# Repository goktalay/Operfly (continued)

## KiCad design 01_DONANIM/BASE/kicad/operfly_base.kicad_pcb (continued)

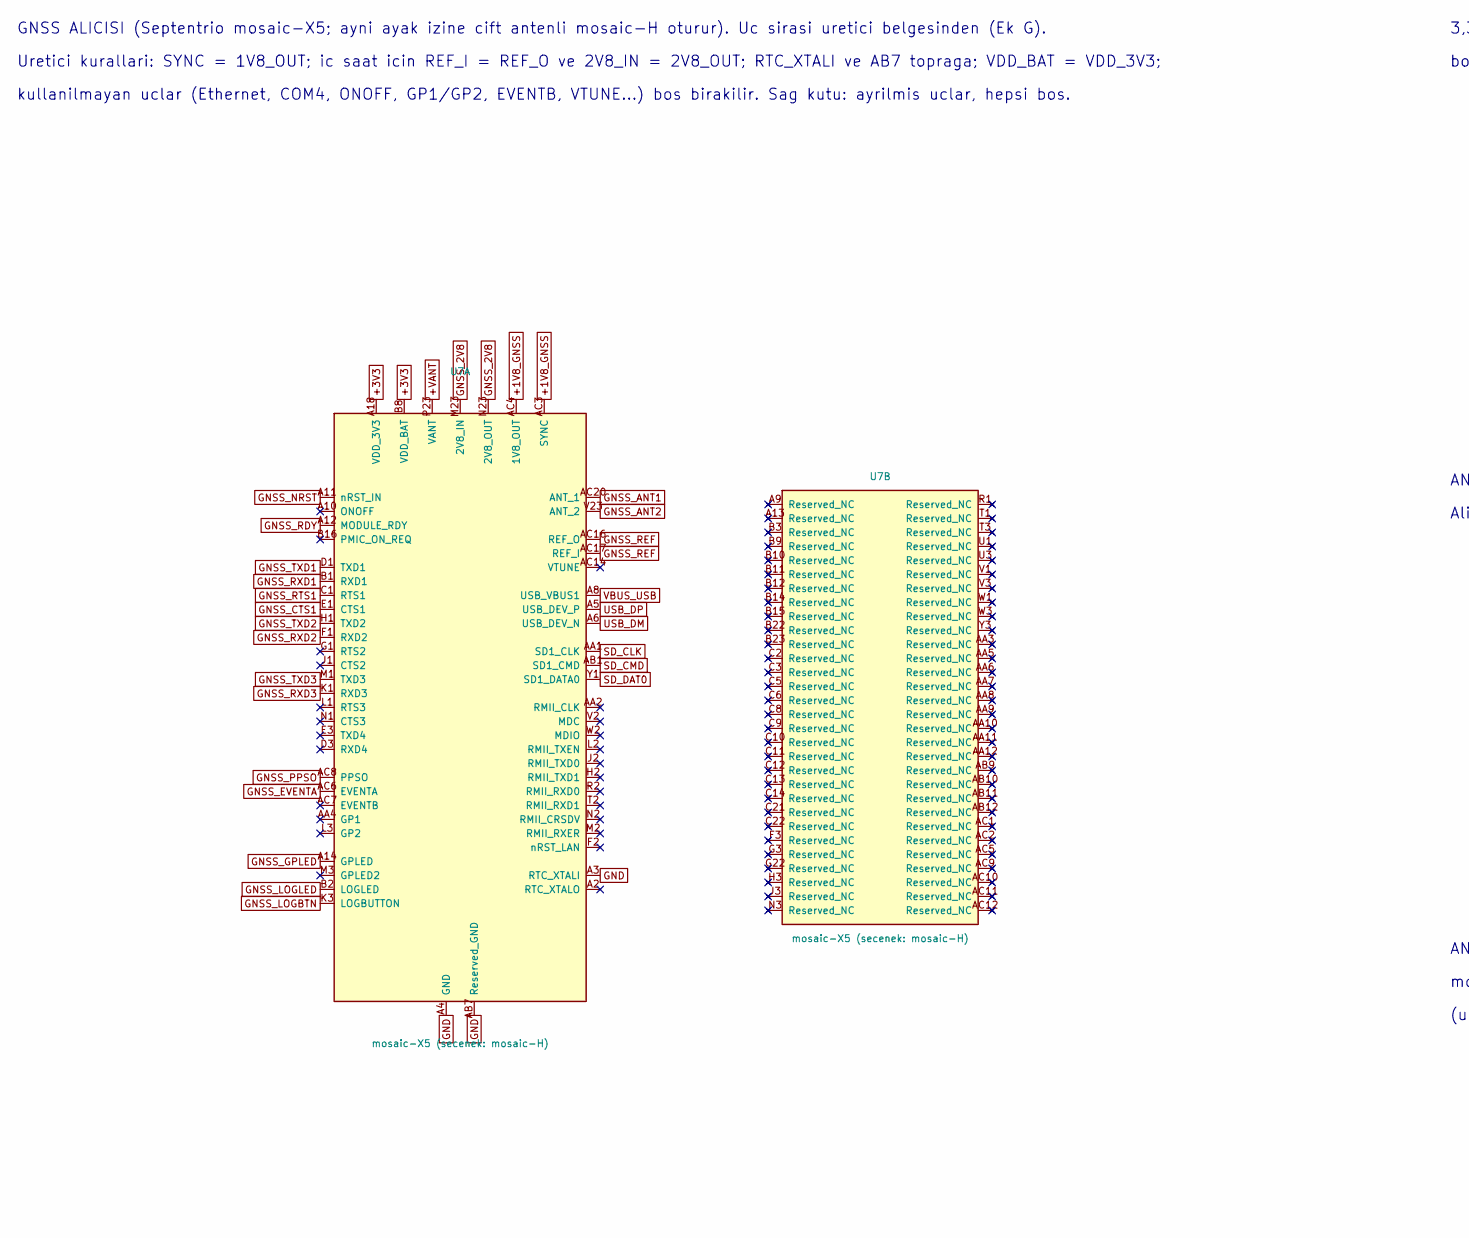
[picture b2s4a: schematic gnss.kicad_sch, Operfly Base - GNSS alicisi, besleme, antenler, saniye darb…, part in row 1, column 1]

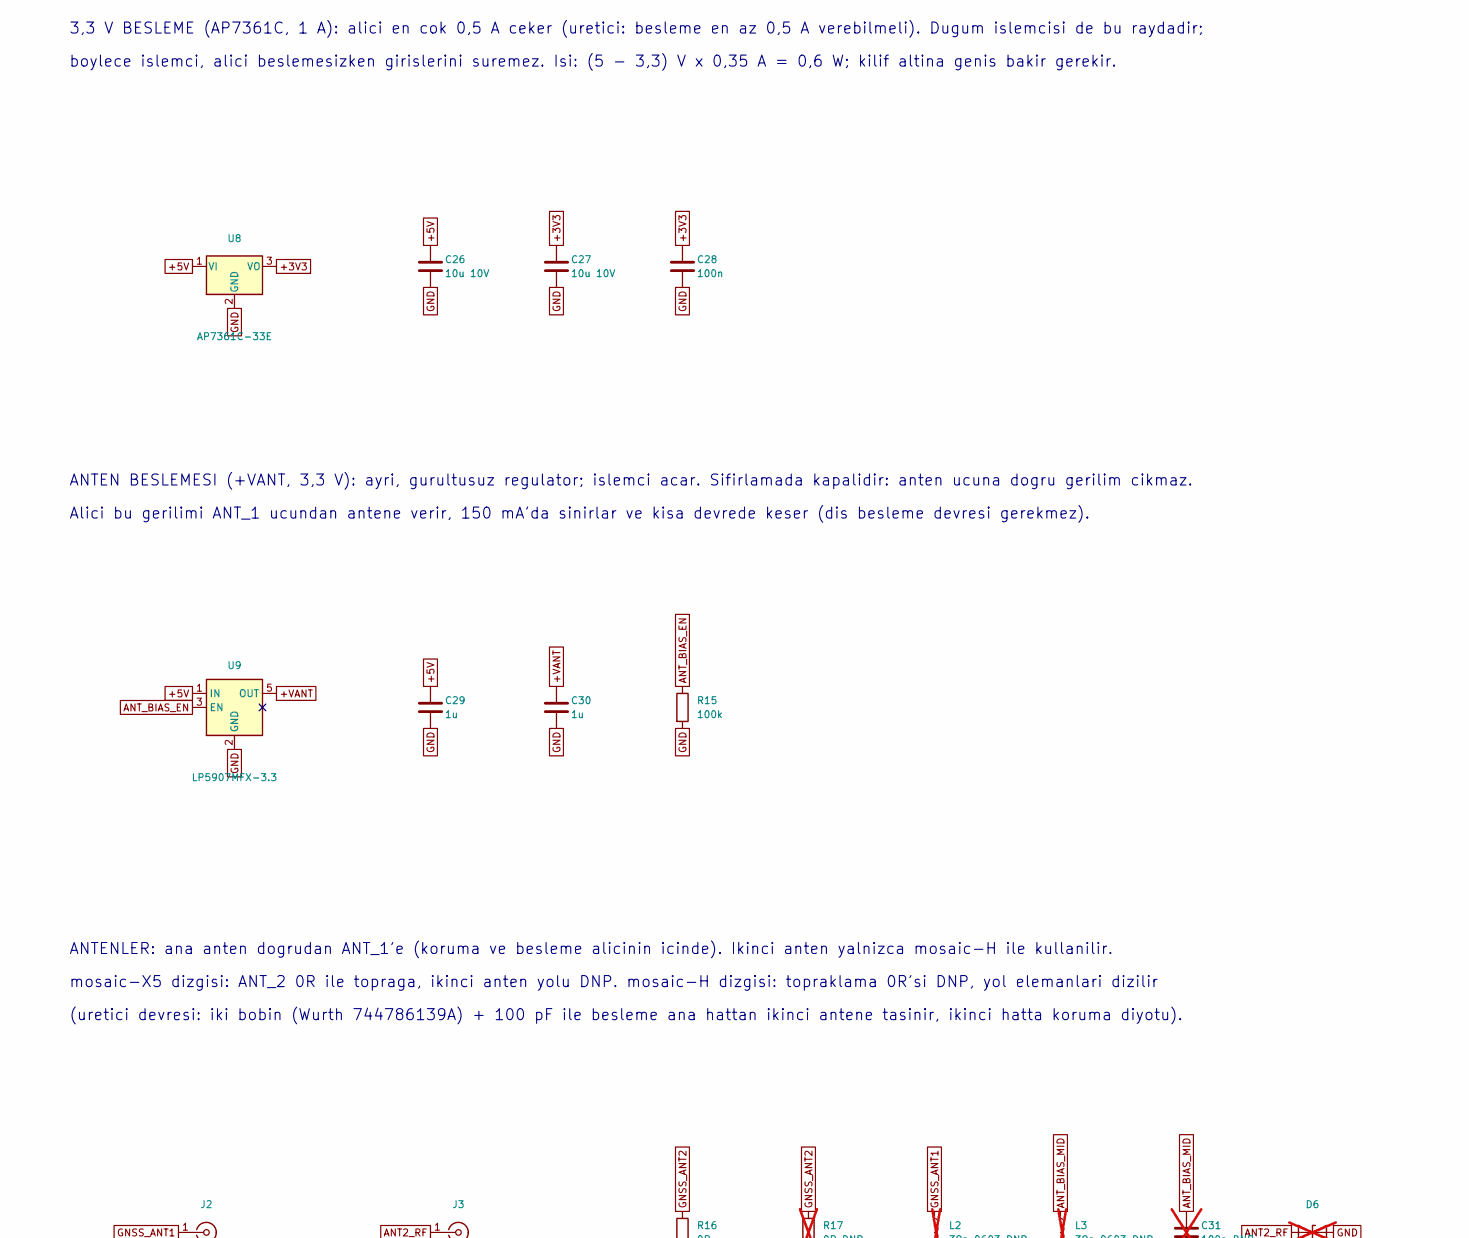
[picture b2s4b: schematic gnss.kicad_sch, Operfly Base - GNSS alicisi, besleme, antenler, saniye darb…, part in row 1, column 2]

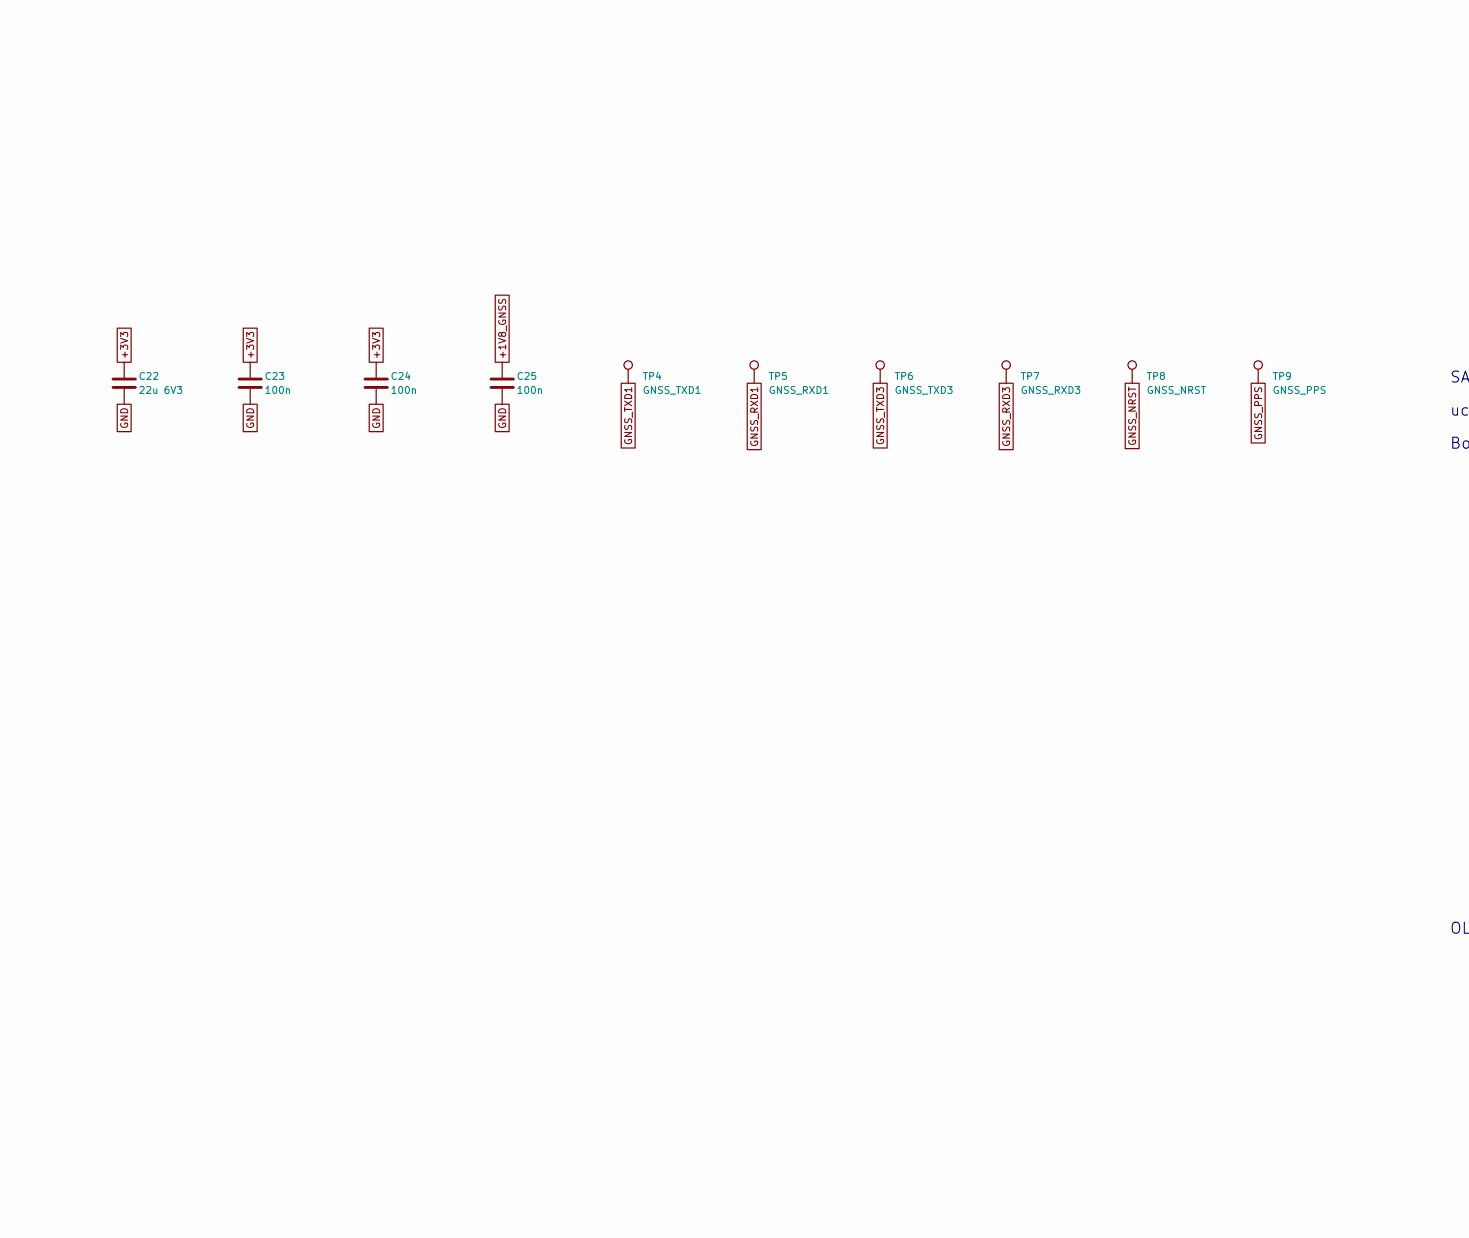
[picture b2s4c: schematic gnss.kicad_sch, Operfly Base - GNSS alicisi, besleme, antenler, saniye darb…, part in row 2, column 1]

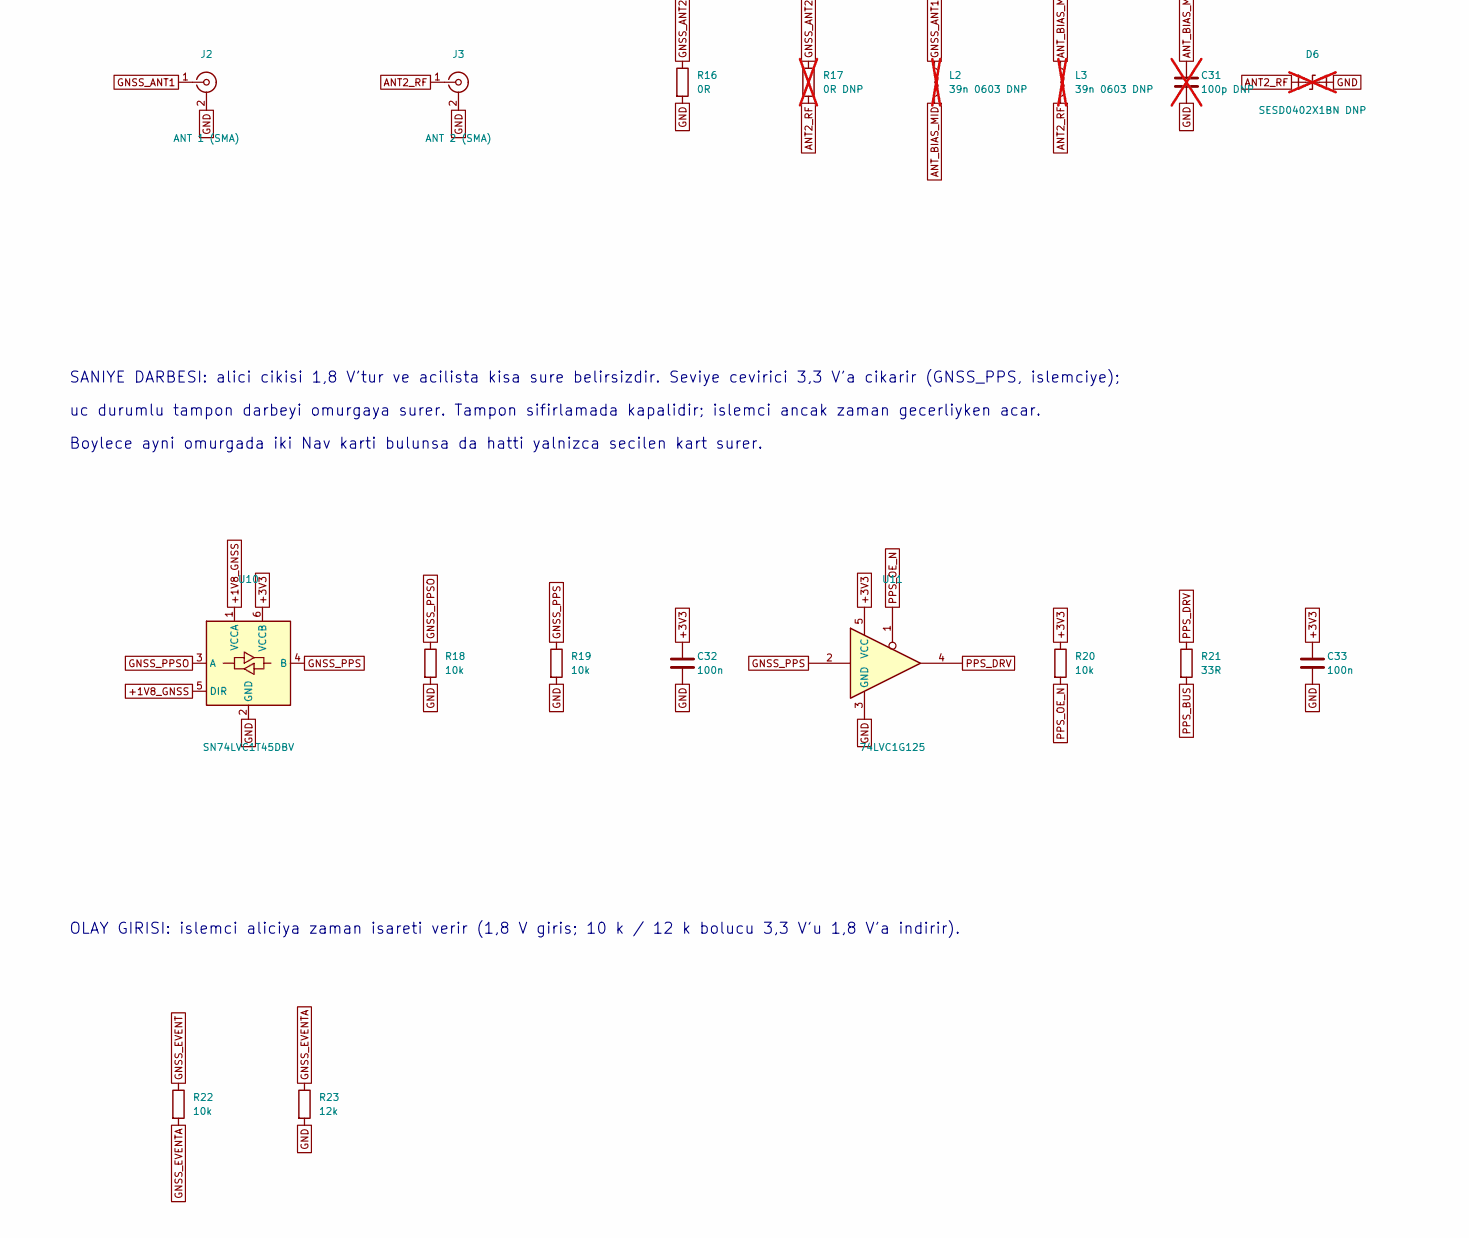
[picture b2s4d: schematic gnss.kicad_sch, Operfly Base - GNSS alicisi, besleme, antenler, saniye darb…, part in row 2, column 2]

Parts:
C22: 22u 6V3; C_0805_2012Metric
C23, C24, C25, C28, C32, C33: 100n; C_0402_1005Metric
C26, C27: 10u 10V; C_0805_2012Metric
C29, C30: 1u; C_0402_1005Metric
C31: 100p DNP; C_0402_1005Metric; not fitted
D6: SESD0402X1BN DNP; D_0402_1005Metric; not fitted
J2: ANT 1 (SMA); SMA_Amphenol_132289_EdgeMount
J3: ANT 2 (SMA); SMA_Amphenol_132289_EdgeMount
L2, L3: 39n 0603 DNP; L_0603_1608Metric; not fitted
R15: 100k; R_0402_1005Metric
R16: 0R; R_0402_1005Metric
R17: 0R DNP; R_0402_1005Metric; not fitted
R18, R19, R20, R22: 10k; R_0402_1005Metric
R21: 33R; R_0402_1005Metric
R23: 12k; R_0402_1005Metric
TP4: GNSS_TXD1; TestPoint_Pad_D1.0mm
TP5: GNSS_RXD1; TestPoint_Pad_D1.0mm
TP6: GNSS_TXD3; TestPoint_Pad_D1.0mm
TP7: GNSS_RXD3; TestPoint_Pad_D1.0mm
TP8: GNSS_NRST; TestPoint_Pad_D1.0mm
TP9: GNSS_PPS; TestPoint_Pad_D1.0mm
U7: mosaic-X5 (secenek: mosaic-H); Septentrio_mosaic_LGA-239_31x31mm_P1.27mm
U8: AP7361C-33E; SOT-223-3_TabPin2
U9: LP5907MFX-3.3; SOT-23-5
U10: SN74LVC1T45DBV; SOT-23-6
U11: 74LVC1G125; SOT-353_SC-70-5

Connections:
+1V8_GNSS: C25.1, U7.AC3 (SYNC), U7.AC4 (1V8_OUT), U10.1 (VCCA), U10.5 (DIR)
+3V3: C22.1, C23.1, C24.1, C27.1, C28.1, C32.1, C33.1, R20.1, U7.A18 (VDD_3V3), U7.A19 (VDD_3V3), U7.A20 (VDD_3V3), U7.B8 (VDD_BAT), U7.B18 (VDD_3V3), U7.B19 (VDD_3V3), U7.B20 (VDD_3V3), U7.C18 (VDD_3V3), U7.C19 (VDD_3V3), U7.C20 (VDD_3V3), U8.3 (VO), U10.6 (VCCB), U11.5 (VCC); also elsewhere on the board
+5V: C26.1, C29.1, U8.1 (VI), U9.1 (IN); also elsewhere on the board
+VANT: C30.1, U7.P23 (VANT), U7.R23 (VANT), U9.5 (OUT)
ANT2_RF: D6.1 (A1), J3.1 (In), L3.2, R17.2
ANT_BIAS_EN: R15.1, U9.3 (EN); also elsewhere on the board
ANT_BIAS_MID: C31.1, L2.2, L3.1
GND: C22.2, C23.2, C24.2, C25.2, C26.2, C27.2, C28.2, C29.2, C30.2, C31.2, C32.2, C33.2, D6.2 (A2), J2.2 (Ext), J3.2 (Ext), R15.2, R16.2, R18.2, R19.2, R23.2, U7.A3 (RTC_XTALI), U7.A4 (GND), U7.A7 (GND), U7.A15 (GND), U7.A16 (GND), U7.A17 (GND), U7.A21 (GND), U7.A22 (GND), U7.A23 (GND), U7.AA13 (GND), U7.AA14 (GND), U7.AA15 (GND), U7.AA16 (GND), U7.AA17 (GND), U7.AA18 (GND), U7.AA19 (GND), U7.AA20 (GND), U7.AA21 (GND), U7.AA22 (GND), U7.AA23 (GND), U7.AB2 (GND), U7.AB3 (GND), U7.AB4 (GND), U7.AB5 (GND), U7.AB6 (GND), U7.AB7 (Reserved_GND), U7.AB8 (GND), U7.AB13 (GND), U7.AB14 (GND), U7.AB15 (GND), U7.AB16 (GND), U7.AB17 (GND), U7.AB18 (GND), U7.AB19 (GND), U7.AB20 (GND), U7.AB21 (GND), U7.AB22 (GND), U7.AB23 (GND), U7.AC13 (GND), U7.AC15 (GND), U7.AC18 (GND), U7.AC19 (GND), U7.AC21 (GND), U7.AC22 (GND), U7.AC23 (GND), U7.B4 (GND), U7.B5 (GND), U7.B6 (GND), U7.B7 (GND), U7.B13 (GND), U7.B17 (GND), U7.B21 (GND), U7.C4 (GND), U7.C7 (GND), U7.C15 (GND), U7.C16 (GND), U7.C17 (GND), U7.C23 (GND), U7.D2 (GND), U7.D21 (GND), U7.D22 (GND), U7.D23 (GND), U7.E2 (GND), U7.E21 (GND), U7.E22 (GND), U7.E23 (GND), U7.F21 (GND), U7.F22 (GND), U7.F23 (GND), U7.G2 (GND), U7.G21 (GND), U7.G23 (GND), U7.H21 (GND), U7.H22 (GND), U7.H23 (GND), U7.J21 (GND), U7.J22 (GND), U7.J23 (GND), U7.K2 (GND), U7.K21 (GND), U7.K22 (GND), U7.K23 (GND), U7.L21 (GND), U7.L22 (GND), U7.L23 (GND), U7.M21 (GND), U7.M22 (GND), U7.N21 (GND), U7.N22 (GND), U7.P1 (GND), U7.P2 (GND), U7.P3 (GND), U7.P21 (GND), U7.P22 (GND), U7.R3 (GND), U7.R21 (GND), U7.R22 (GND), U7.T21 (GND), U7.T22 (GND), U7.T23 (GND), U7.U2 (GND), U7.U21 (GND), U7.U22 (GND), U7.U23 (GND), U7.V21 (GND), U7.V22 (GND), U7.W21 (GND), U7.W22 (GND), U7.W23 (GND), U7.Y2 (GND), U7.Y21 (GND), U7.Y22 (GND), U7.Y23 (GND), U8.2 (GND), U9.2 (GND), U10.2 (GND), U11.3 (GND); also elsewhere on the board
GNSS_2V8: U7.M23 (2V8_IN), U7.N23 (2V8_OUT)
GNSS_ANT1: J2.1 (In), L2.1, U7.AC20 (ANT_1)
GNSS_ANT2: R16.1, R17.1, U7.V23 (ANT_2)
GNSS_CTS1: U7.E1 (CTS1); also elsewhere on the board
GNSS_EVENT: R22.1; also elsewhere on the board
GNSS_EVENTA: R22.2, R23.1, U7.AC6 (EVENTA)
GNSS_GPLED: U7.A14 (GPLED); also elsewhere on the board
GNSS_LOGBTN: U7.K3 (LOGBUTTON); also elsewhere on the board
GNSS_LOGLED: U7.B2 (LOGLED); also elsewhere on the board
GNSS_NRST: TP8.1, U7.A11 (nRST_IN); also elsewhere on the board
GNSS_PPS: R19.1, TP9.1, U10.4 (B), U11.2; also elsewhere on the board
GNSS_PPSO: R18.1, U7.AC8 (PPSO), U10.3 (A)
GNSS_RDY: U7.A12 (MODULE_RDY); also elsewhere on the board
GNSS_REF: U7.AC16 (REF_O), U7.AC17 (REF_I)
GNSS_RTS1: U7.C1 (RTS1); also elsewhere on the board
GNSS_RXD1: TP5.1, U7.B1 (RXD1); also elsewhere on the board
GNSS_RXD2: U7.F1 (RXD2); also elsewhere on the board
GNSS_RXD3: TP7.1, U7.K1 (RXD3)
GNSS_TXD1: TP4.1, U7.D1 (TXD1); also elsewhere on the board
GNSS_TXD2: U7.H1 (TXD2); also elsewhere on the board
GNSS_TXD3: TP6.1, U7.M1 (TXD3)
PPS_BUS: R21.2; also elsewhere on the board
PPS_DRV: R21.1, U11.4
PPS_OE_N: R20.2, U11.1; also elsewhere on the board
SD_CLK: U7.AA1 (SD1_CLK); also elsewhere on the board
SD_CMD: U7.AB1 (SD1_CMD); also elsewhere on the board
SD_DAT0: U7.Y1 (SD1_DATA0); also elsewhere on the board
USB_DM: U7.A6 (USB_DEV_N); also elsewhere on the board
USB_DP: U7.A5 (USB_DEV_P); also elsewhere on the board
VBUS_USB: U7.A8 (USB_VBUS1); also elsewhere on the board

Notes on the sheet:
uc durumlu tampon darbeyi omurgaya surer. Tampon sifirlamada kapalidir; islemci ancak zaman gecerliyken acar.
GNSS ALICISI (Septentrio mosaic-X5; ayni ayak izine cift antenli mosaic-H oturur). Uc sirasi uretici belgesinden (Ek G).
(uretici devresi: iki bobin (Wurth 744786139A) + 100 pF ile besleme ana hattan ikinci antene tasinir, ikinci hatta koruma diyotu).
ANTEN BESLEMESI (+VANT, 3,3 V): ayri, gurultusuz regulator; islemci acar. Sifirlamada kapalidir: anten ucuna dogru gerilim cikmaz.
Uretici kurallari: SYNC = 1V8_OUT; ic saat icin REF_I = REF_O ve 2V8_IN = 2V8_OUT; RTC_XTALI ve AB7 topraga; VDD_BAT = VDD_3V3;
Boylece ayni omurgada iki Nav karti bulunsa da hatti yalnizca secilen kart surer.
3,3 V BESLEME (AP7361C, 1 A): alici en cok 0,5 A ceker (uretici: besleme en az 0,5 A verebilmeli). Dugum islemcisi de bu raydadir;
kullanilmayan uclar (Ethernet, COM4, ONOFF, GP1/GP2, EVENTB, VTUNE...) bos birakilir. Sag kutu: ayrilmis uclar, hepsi bos.
SANIYE DARBESI: alici cikisi 1,8 V'tur ve acilista kisa sure belirsizdir. Seviye cevirici 3,3 V'a cikarir (GNSS_PPS, islemciye);
Alici bu gerilimi ANT_1 ucundan antene verir, 150 mA'da sinirlar ve kisa devrede keser (dis besleme devresi gerekmez).
boylece islemci, alici beslemesizken girislerini suremez. Isi: (5 - 3,3) V x 0,35 A = 0,6 W; kilif altina genis bakir gerekir.
OLAY GIRISI: islemci aliciya zaman isareti verir (1,8 V giris; 10 k / 12 k bolucu 3,3 V'u 1,8 V'a indirir).
ANTENLER: ana anten dogrudan ANT_1'e (koruma ve besleme alicinin icinde). Ikinci anten yalnizca mosaic-H ile kullanilir.
mosaic-X5 dizgisi: ANT_2 0R ile topraga, ikinci anten yolu DNP. mosaic-H dizgisi: topraklama 0R'si DNP, yol elemanlari dizilir

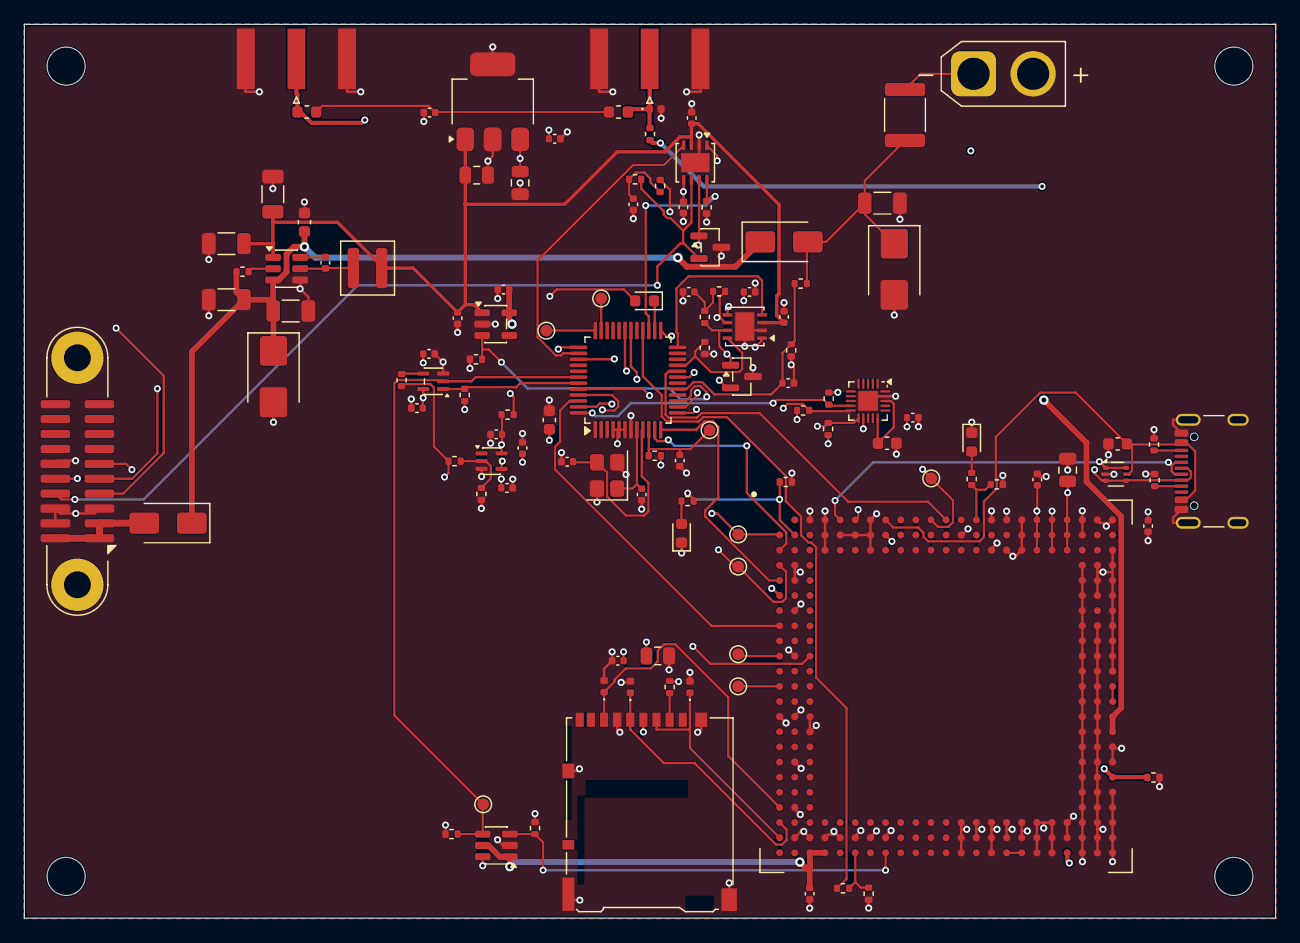
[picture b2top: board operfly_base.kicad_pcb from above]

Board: 4 copper layers, 105.0 x 75.0 mm, 119 parts (0 on the bottom side), 76 nets.

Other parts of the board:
H1, H2, H3, H4: M3; MountingHole_3.2mm_M3

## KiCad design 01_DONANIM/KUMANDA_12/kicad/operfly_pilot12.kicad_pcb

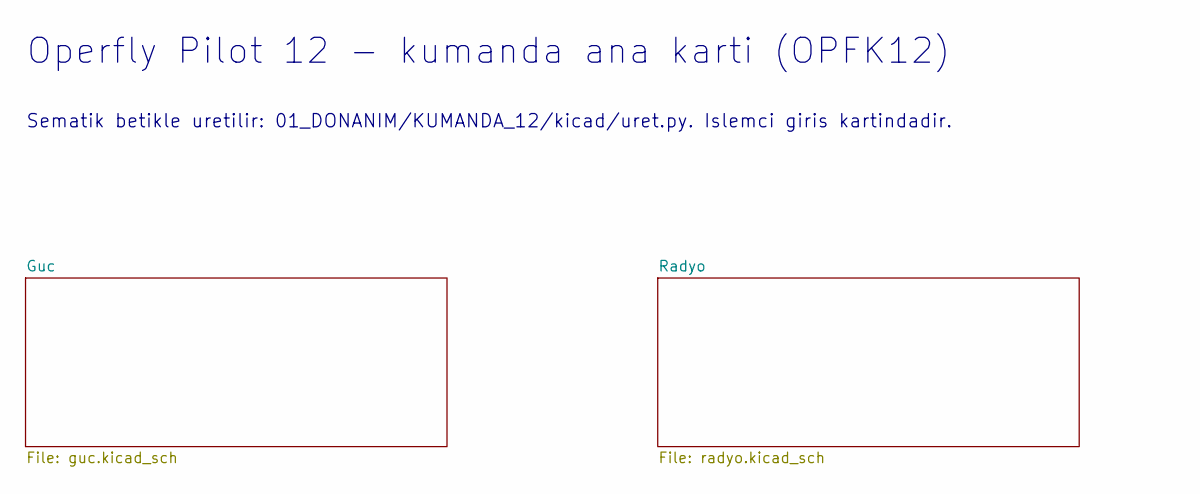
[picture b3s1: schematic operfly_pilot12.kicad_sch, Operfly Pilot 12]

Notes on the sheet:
Operfly Pilot 12 - kumanda ana karti (OPFK12)
Sematik betikle uretilir: 01_DONANIM/KUMANDA_12/kicad/uret.py. Islemci giris kartindadir.

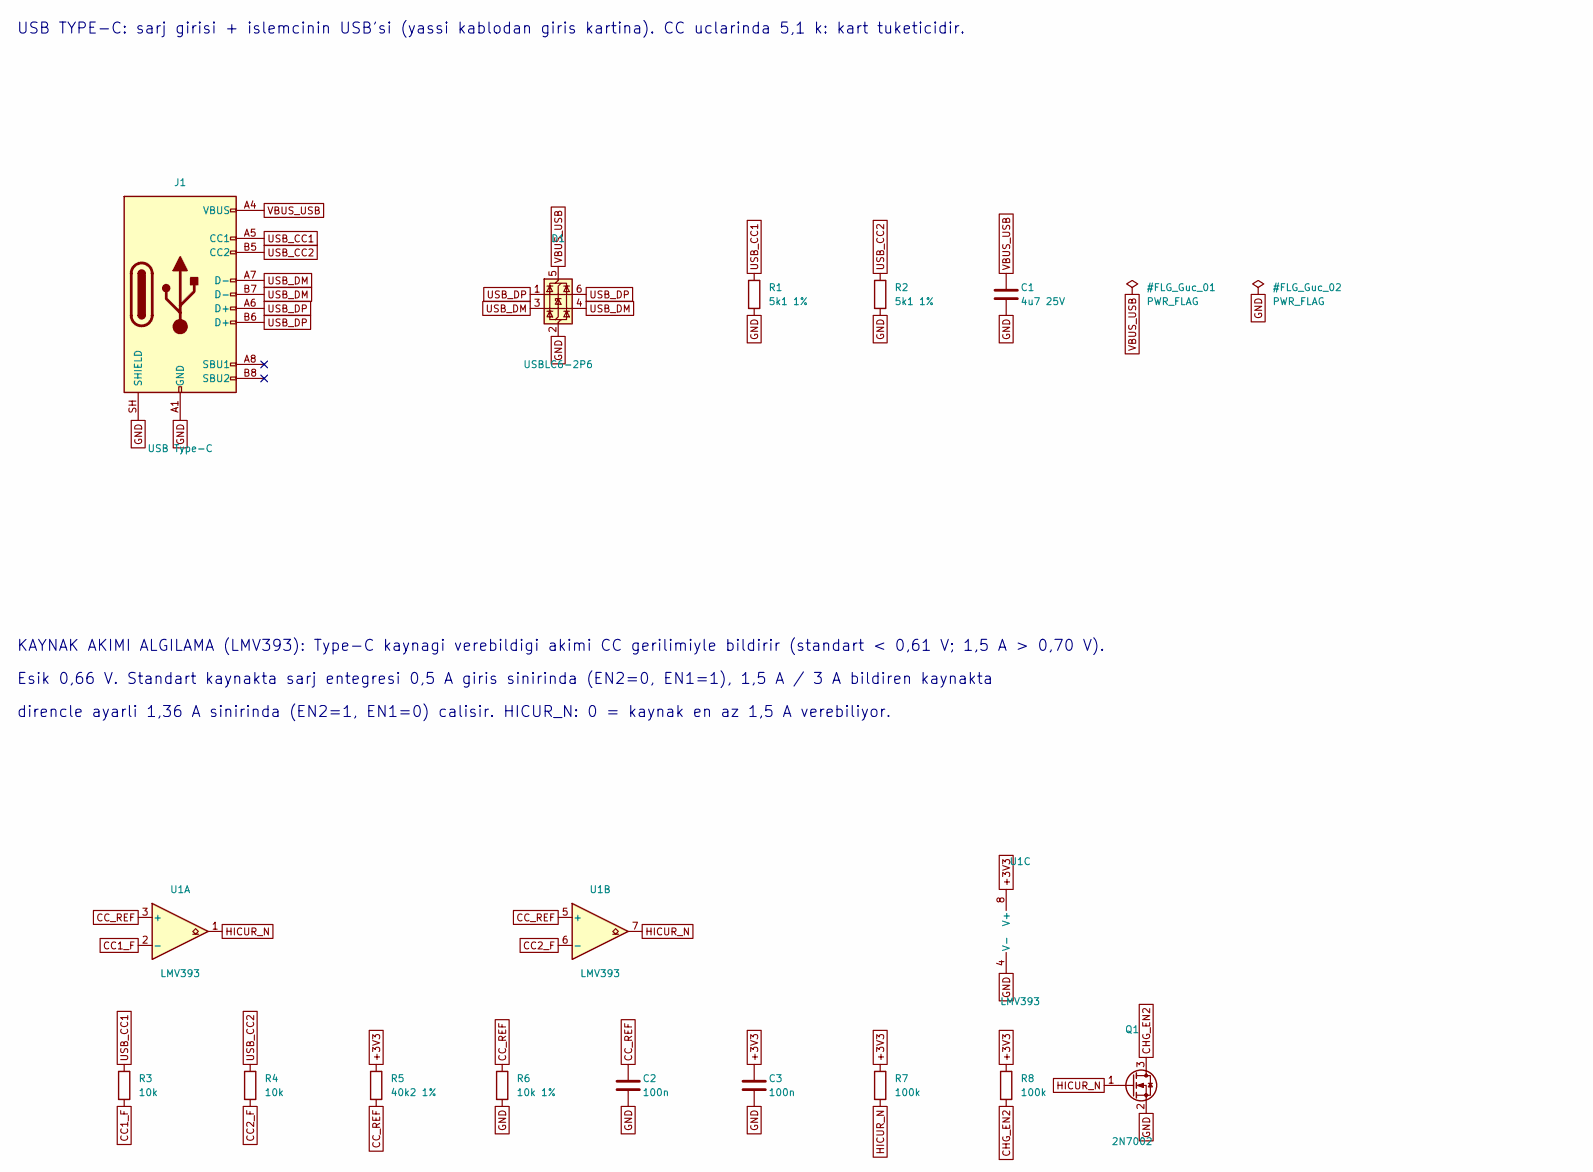
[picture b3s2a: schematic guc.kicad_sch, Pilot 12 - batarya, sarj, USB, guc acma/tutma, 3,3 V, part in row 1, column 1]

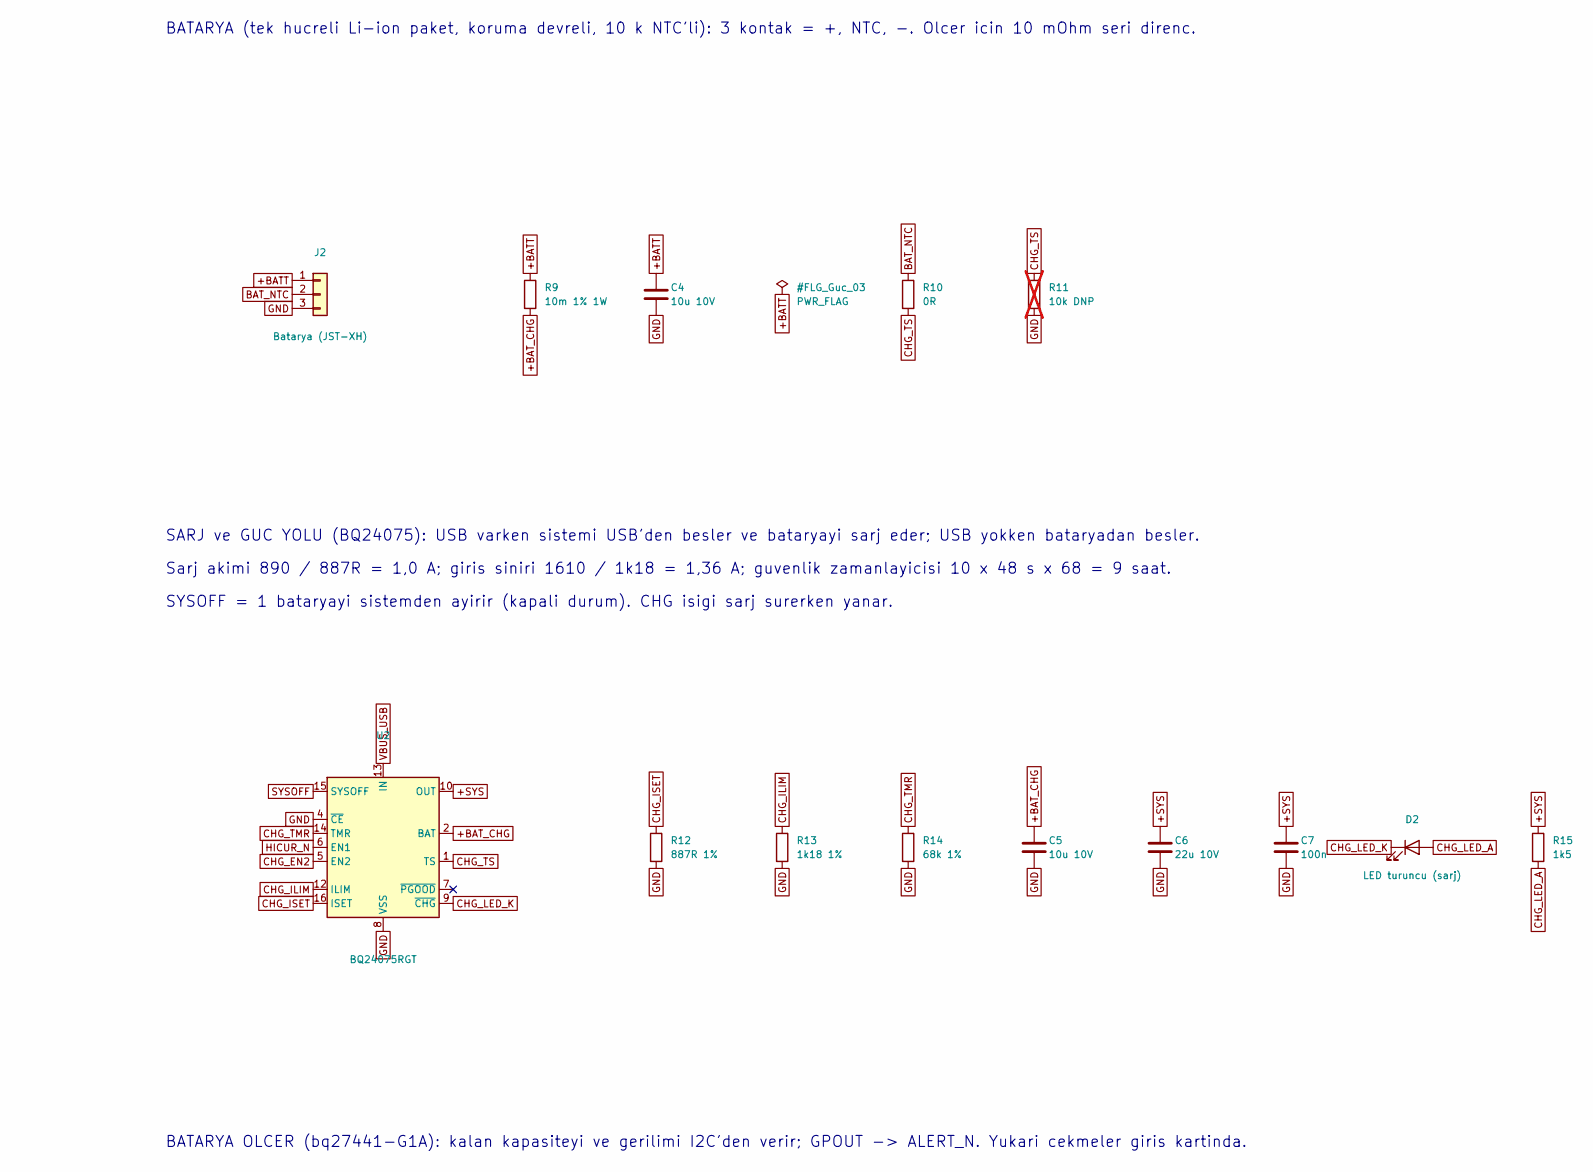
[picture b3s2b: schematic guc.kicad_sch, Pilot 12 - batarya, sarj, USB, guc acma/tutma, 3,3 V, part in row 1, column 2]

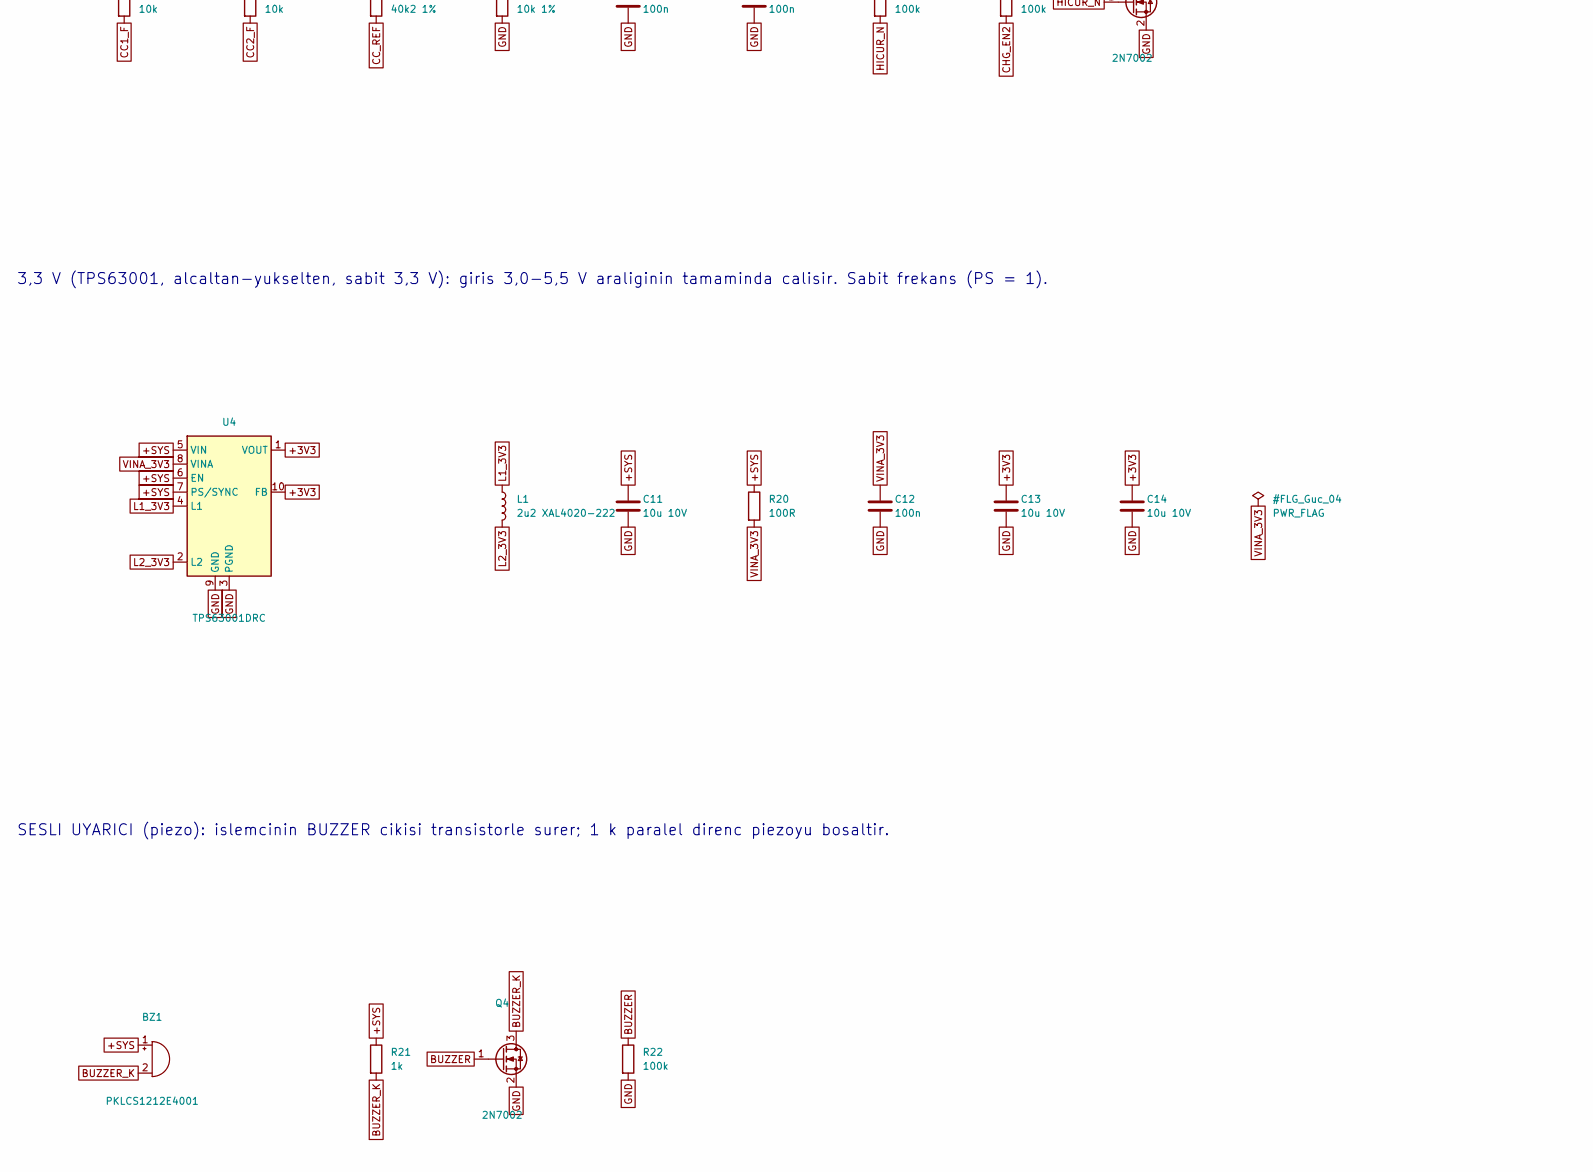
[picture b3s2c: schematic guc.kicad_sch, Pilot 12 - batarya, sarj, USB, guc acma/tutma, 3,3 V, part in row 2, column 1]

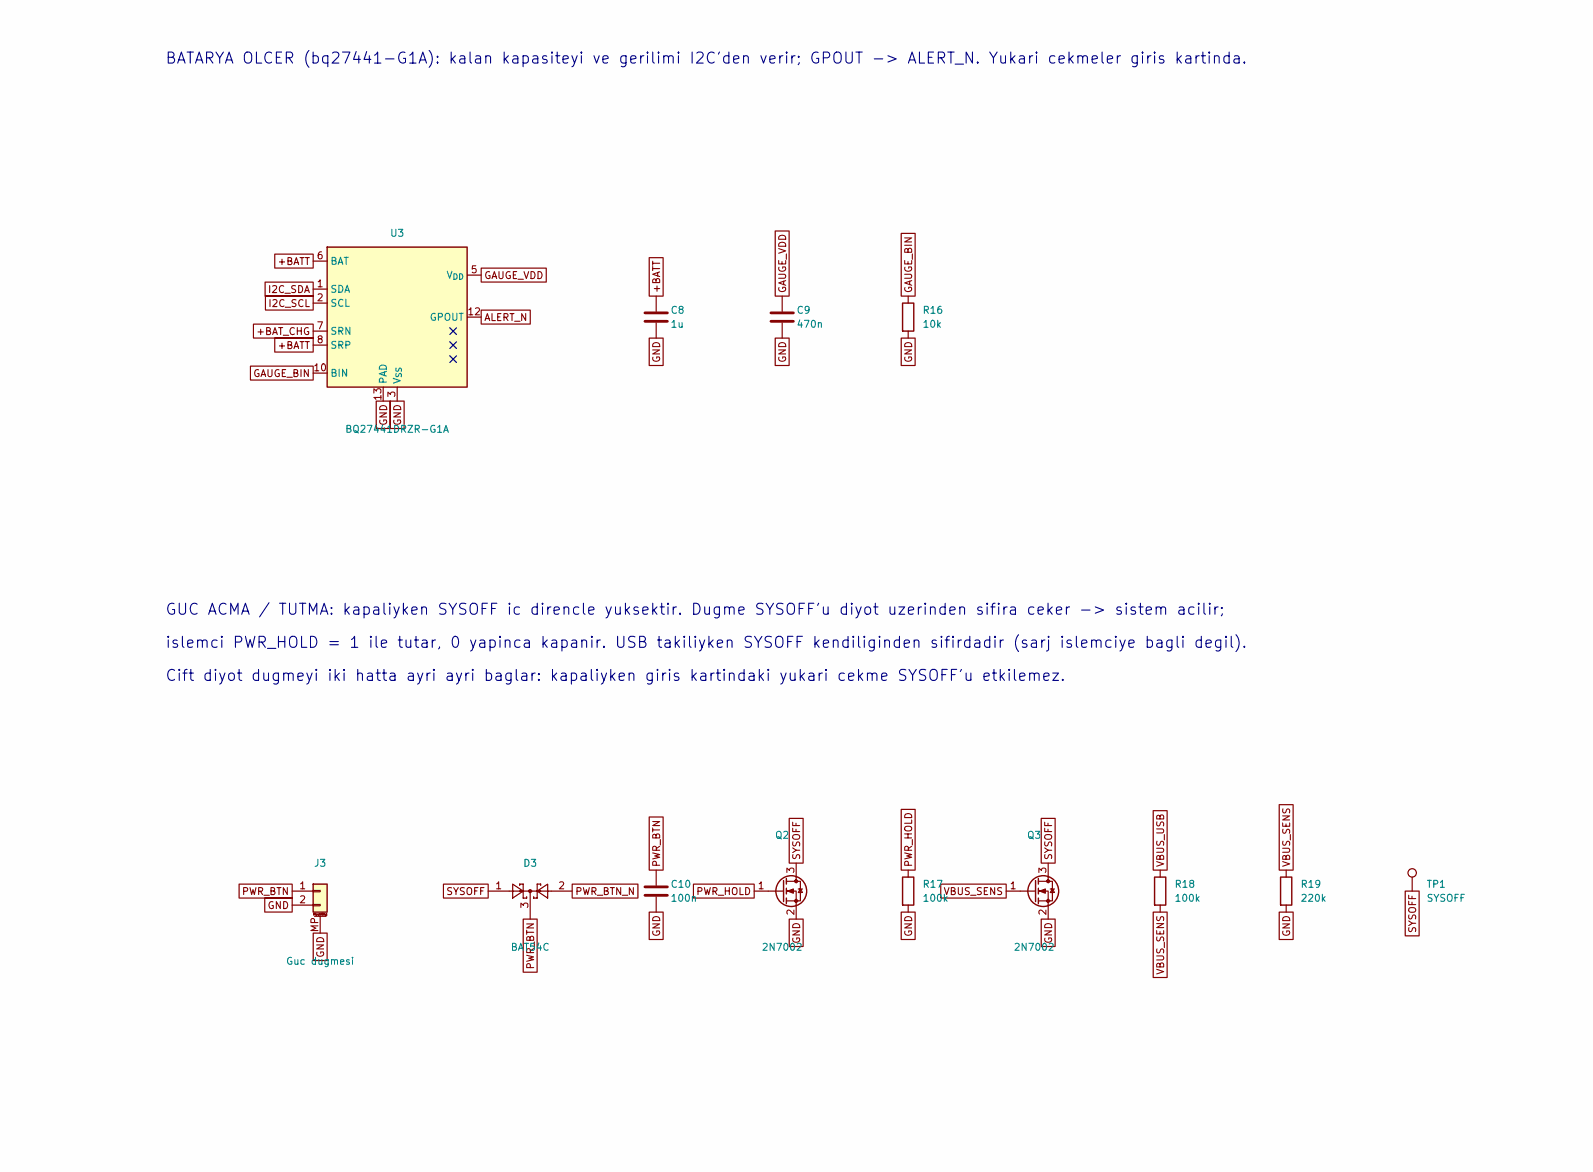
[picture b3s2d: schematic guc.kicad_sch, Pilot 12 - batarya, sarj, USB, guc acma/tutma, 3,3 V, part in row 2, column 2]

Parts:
BZ1: PKLCS1212E4001; Buzzer_Murata_PKLCS1212E
C1: 4u7 25V; C_0805_2012Metric
C2, C3, C7, C10, C12: 100n; C_0402_1005Metric
C4, C5, C11, C13, C14: 10u 10V; C_0805_2012Metric
C6: 22u 10V; C_1206_3216Metric
C8: 1u; C_0402_1005Metric
C9: 470n; C_0402_1005Metric
D1: USBLC6-2P6; SOT-666
D2: LED turuncu (sarj); LED_0603_1608Metric
D3: BAT54C; SOT-23
J1: USB Type-C; USB_C_Receptacle_GCT_USB4105-xx-A_16P_TopMnt_Horizontal
J2: Batarya (JST-XH); JST_XH_B3B-XH-A_1x03_P2.50mm_Vertical
J3: Guc dugmesi; JST_GH_SM02B-GHS-TB_1x02-1MP_P1.25mm_Horizontal
L1: 2u2 XAL4020-222; L_Coilcraft_XAL4020-XXX
Q1, Q2, Q3, Q4: 2N7002; SOT-23
R1, R2: 5k1 1%; R_0402_1005Metric
R3, R4, R16: 10k; R_0402_1005Metric
R5: 40k2 1%; R_0402_1005Metric
R6: 10k 1%; R_0402_1005Metric
R7, R8, R17, R18, R22: 100k; R_0402_1005Metric
R9: 10m 1% 1W; R_1206_3216Metric
R10: 0R; R_0402_1005Metric
R11: 10k DNP; R_0402_1005Metric; not fitted
R12: 887R 1%; R_0402_1005Metric
R13: 1k18 1%; R_0402_1005Metric
R14: 68k 1%; R_0402_1005Metric
R15: 1k5; R_0402_1005Metric
R19: 220k; R_0402_1005Metric
R20: 100R; R_0402_1005Metric
R21: 1k; R_0402_1005Metric
TP1: SYSOFF; TestPoint_Pad_D1.0mm
U1: LMV393; TSSOP-8_4.4x3mm_P0.65mm
U2: BQ24075RGT; VQFN-16-1EP_3x3mm_P0.5mm_EP1.6x1.6mm
U3: BQ27441DRZR-G1A; Texas_S-PDSO-N12
U4: TPS63001DRC; Texas_DRC0010J_ThermalVias

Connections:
+3V3: C3.1, C13.1, C14.1, R5.1, R7.1, R8.1, U1.8 (V+), U4.1 (VOUT), U4.10 (FB); also elsewhere on the board
+BATT: C4.1, C8.1, J2.1, R9.1, U3.6 (BAT), U3.8 (SRP)
+BAT_CHG: C5.1, R9.2, U2.2 (BAT), U2.3 (BAT), U3.7 (SRN)
+SYS: BZ1.1 (+), C6.1, C7.1, C11.1, R15.1, R20.1, R21.1, U2.10 (OUT), U2.11 (OUT), U4.5 (VIN), U4.6 (EN), U4.7 (PS/SYNC); also elsewhere on the board
ALERT_N: U3.12 (GPOUT); also elsewhere on the board
BAT_NTC: J2.2, R10.1
BUZZER: Q4.1 (G), R22.1; also elsewhere on the board
BUZZER_K: BZ1.2 (-), Q4.3 (D), R21.2
CC1_F: R3.2, U1.2 (-)
CC2_F: R4.2, U1.6 (-)
CC_REF: C2.1, R5.2, R6.1, U1.3 (+), U1.5 (+)
CHG_EN2: Q1.3 (D), R8.2, U2.5 (EN2)
CHG_ILIM: R13.1, U2.12 (ILIM)
CHG_ISET: R12.1, U2.16 (ISET)
CHG_LED_A: D2.2 (A), R15.2
CHG_LED_K: D2.1 (K), U2.9 (~CHG)
CHG_TMR: R14.1, U2.14 (TMR)
CHG_TS: R10.2, R11.1, U2.1 (TS)
GAUGE_BIN: R16.1, U3.10 (BIN)
GAUGE_VDD: C9.1, U3.5 (V_{DD})
GND: C1.2, C2.2, C3.2, C4.2, C5.2, C6.2, C7.2, C8.2, C9.2, C10.2, C11.2, C12.2, C13.2, C14.2, D1.2 (GND), J1.A1 (GND), J1.A12 (GND), J1.B1 (GND), J1.B12 (GND), J1.SH (SHIELD), J2.3, J3.2, J3.MP (MountPin), Q1.2 (S), Q2.2 (S), Q3.2 (S), Q4.2 (S), R1.2, R2.2, R6.2, R11.2, R12.2, R13.2, R14.2, R16.2, R17.2, R19.2, R22.2, U1.4 (V-), U2.4 (~CE), U2.8 (VSS), U2.17 (VSS), U3.3 (V_{SS}), U3.13 (PAD), U4.3 (PGND), U4.9 (GND), U4.11 (PGND); also elsewhere on the board
HICUR_N: Q1.1 (G), R7.2, U1.1, U1.7, U2.6 (EN1)
I2C_SCL: U3.2 (SCL); also elsewhere on the board
I2C_SDA: U3.1 (SDA); also elsewhere on the board
L1_3V3: L1.1, U4.4 (L1)
L2_3V3: L1.2, U4.2 (L2)
PWR_BTN: C10.1, D3.3, J3.1
PWR_BTN_N: D3.2; also elsewhere on the board
PWR_HOLD: Q2.1 (G), R17.1; also elsewhere on the board
SYSOFF: D3.1, Q2.3 (D), Q3.3 (D), TP1.1, U2.15 (SYSOFF)
USB_CC1: J1.A5 (CC1), R1.1, R3.1
USB_CC2: J1.B5 (CC2), R2.1, R4.1
USB_DM: D1.3 (I/O2), D1.4 (I/O2), J1.A7 (D-), J1.B7 (D-); also elsewhere on the board
USB_DP: D1.1 (I/O1), D1.6 (I/O1), J1.A6 (D+), J1.B6 (D+); also elsewhere on the board
VBUS_SENS: Q3.1 (G), R18.2, R19.1
VBUS_USB: C1.1, D1.5 (VBUS), J1.A4 (VBUS), J1.A9 (VBUS), J1.B4 (VBUS), J1.B9 (VBUS), R18.1, U2.13 (IN)
VINA_3V3: C12.1, R20.2, U4.8 (VINA)

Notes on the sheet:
Sarj akimi 890 / 887R = 1,0 A; giris siniri 1610 / 1k18 = 1,36 A; guvenlik zamanlayicisi 10 x 48 s x 68 = 9 saat.
SARJ ve GUC YOLU (BQ24075): USB varken sistemi USB'den besler ve bataryayi sarj eder; USB yokken bataryadan besler.
Esik 0,66 V. Standart kaynakta sarj entegresi 0,5 A giris sinirinda (EN2=0, EN1=1), 1,5 A / 3 A bildiren kaynakta
islemci PWR_HOLD = 1 ile tutar, 0 yapinca kapanir. USB takiliyken SYSOFF kendiliginden sifirdadir (sarj islemciye bagli degil).
BATARYA (tek hucreli Li-ion paket, koruma devreli, 10 k NTC'li): 3 kontak = +, NTC, -. Olcer icin 10 mOhm seri direnc.
SYSOFF = 1 bataryayi sistemden ayirir (kapali durum). CHG isigi sarj surerken yanar.
direncle ayarli 1,36 A sinirinda (EN2=1, EN1=0) calisir. HICUR_N: 0 = kaynak en az 1,5 A verebiliyor.
GUC ACMA / TUTMA: kapaliyken SYSOFF ic direncle yuksektir. Dugme SYSOFF'u diyot uzerinden sifira ceker -> sistem acilir;
Cift diyot dugmeyi iki hatta ayri ayri baglar: kapaliyken giris kartindaki yukari cekme SYSOFF'u etkilemez.
KAYNAK AKIMI ALGILAMA (LMV393): Type-C kaynagi verebildigi akimi CC gerilimiyle bildirir (standart < 0,61 V; 1,5 A > 0,70 V).
BATARYA OLCER (bq27441-G1A): kalan kapasiteyi ve gerilimi I2C'den verir; GPOUT -> ALERT_N. Yukari cekmeler giris kartinda.
3,3 V (TPS63001, alcaltan-yukselten, sabit 3,3 V): giris 3,0-5,5 V araliginin tamaminda calisir. Sabit frekans (PS = 1).
SESLI UYARICI (piezo): islemcinin BUZZER cikisi transistorle surer; 1 k paralel direnc piezoyu bosaltir.
USB TYPE-C: sarj girisi + islemcinin USB'si (yassi kablodan giris kartina). CC uclarinda 5,1 k: kart tuketicidir.
